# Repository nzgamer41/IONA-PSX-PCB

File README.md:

# IONA-PSX-PCB
This repository contains the EAGLE files for the v1 IONA-PSX Arduino Shield PCB. It's a simple design that shouldn't be too hard to follow.

## Files
- 2-Layer-JLC.cam is the CAM file from JLCPCB for generating correct gerber files from the EAGLE files
- IONA-PSX.brd is the Board design file.
- IONA-PSX.sch is the schematic file.
This uses the SparkFun EAGLE library, as well as the Open Source Hardware logo.

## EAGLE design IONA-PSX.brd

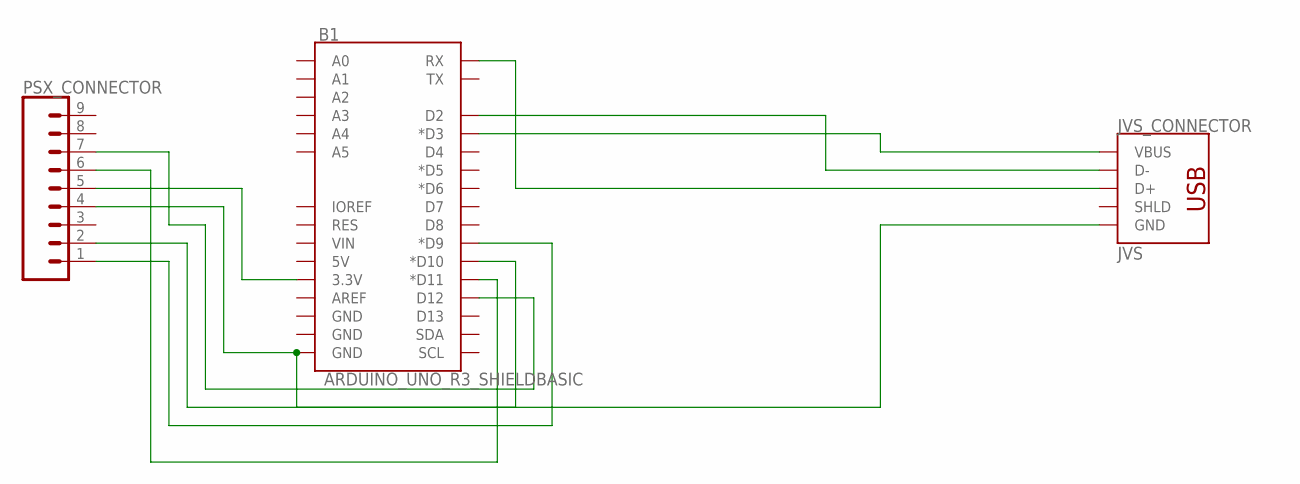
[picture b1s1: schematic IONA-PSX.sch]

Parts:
B1: ARDUINO_UNO_R3_SHIELDBASIC; UNO_R3_SHIELD
JVS_CONNECTOR: JVS; USB-B-PTH
PSX_CONNECTOR: CONN_09; 1X09

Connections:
unnamed: B1.D2, JVS_CONNECTOR.D-
unnamed: B1.RX, JVS_CONNECTOR.D+
unnamed: B1.D3 (*D3), JVS_CONNECTOR.VBUS
unnamed: B1.GND@0 (GND), JVS_CONNECTOR.GND, PSX_CONNECTOR.4
unnamed: B1.D9 (*D9), PSX_CONNECTOR.1
unnamed: B1.D10 (*D10), PSX_CONNECTOR.2
unnamed: B1.3.3V, PSX_CONNECTOR.5
unnamed: B1.D11 (*D11), PSX_CONNECTOR.6
unnamed: B1.D12, PSX_CONNECTOR.7

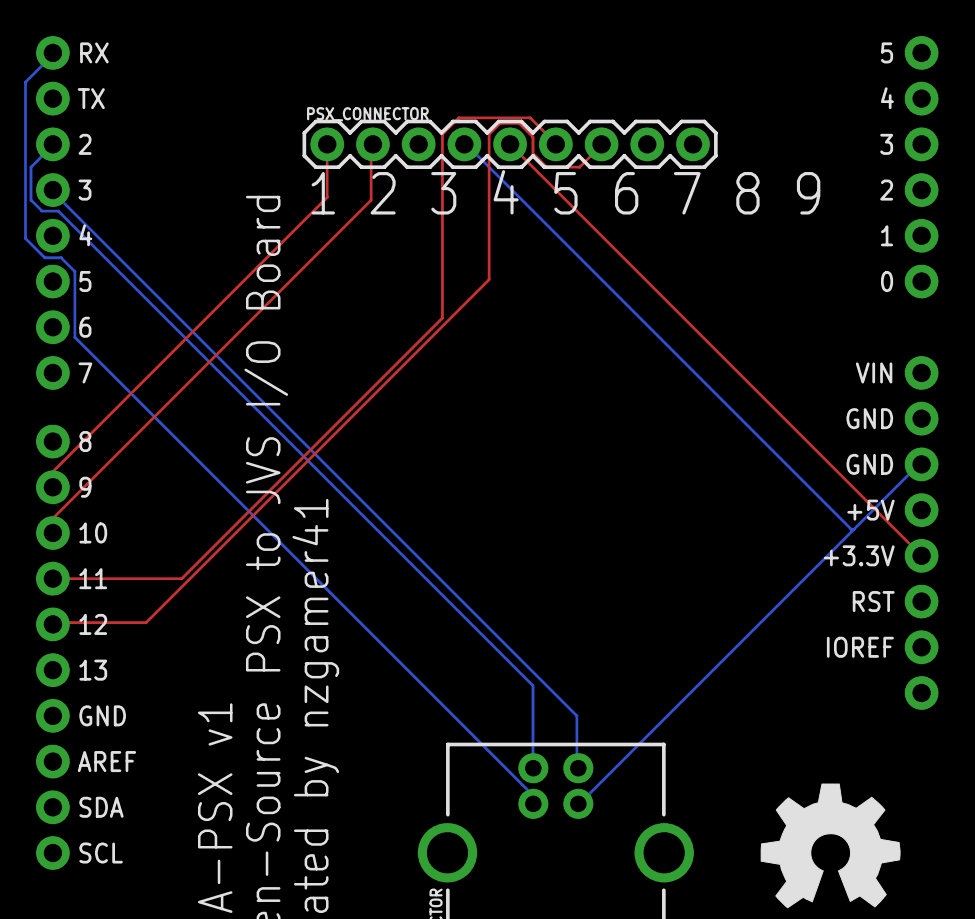
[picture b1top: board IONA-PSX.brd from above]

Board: 2 copper layers, 4 parts (0 on the bottom side), 9 nets.

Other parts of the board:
U$1: OSHW_8MM

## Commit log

2020-09-14 Create LICENSE
2020-09-14 added BOM

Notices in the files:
parts and their libraries:
SparkFun-Boards: Licensing: Creative Commons ShareAlike 4.0 International - https://creativecommons.org/licenses/by-sa/4.0
